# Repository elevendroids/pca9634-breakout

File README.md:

# PCA9634 Breakout Board

Small board for the 8 channel I2C-bus PWM LED driver from NXP - PCA9634 [Datasheet](https://www.nxp.com/docs/en/data-sheet/PCA9634.pdf)

Designed in KiCad 5.1.6

Schematic: [PDF](docs/pca9634-breakout.pdf)

License: [CC BY-SA 4.0](https://creativecommons.org/licenses/by-sa/4.0/)

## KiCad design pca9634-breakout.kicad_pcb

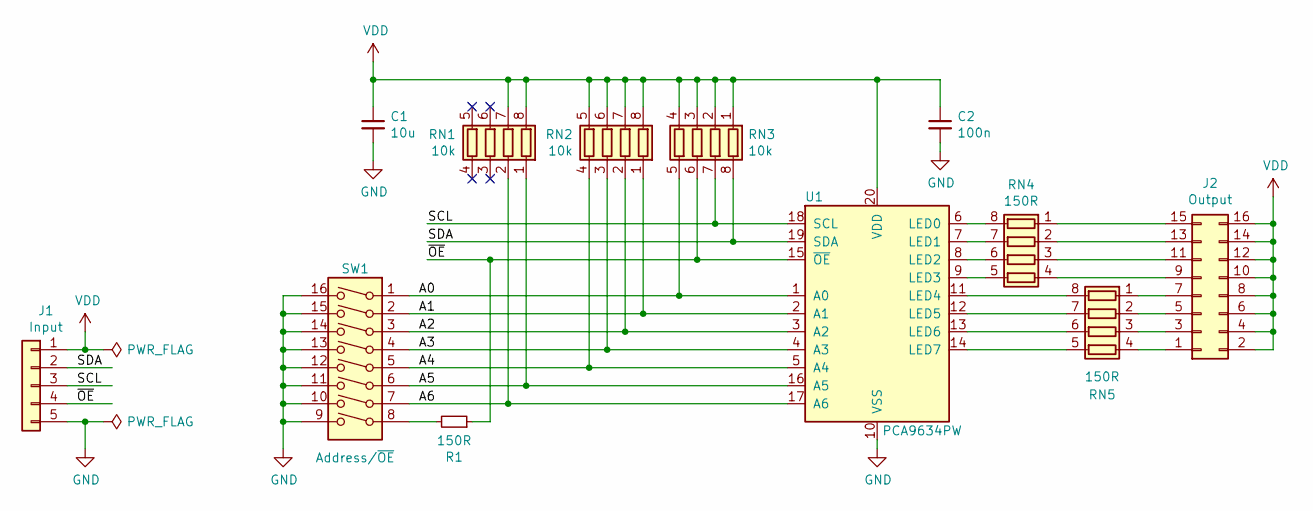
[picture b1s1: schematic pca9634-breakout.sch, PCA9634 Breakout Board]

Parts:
C1: 10u; C_0805_2012Metric
C2: 100n; C_0603_1608Metric
J1: Input; PinHeader_1x05_P2.54mm_Vertical
J2: Output; PinHeader_2x08_P2.54mm_Vertical
R1: 150R; R_0603_1608Metric
RN1, RN2, RN3: 10k; R_Array_Convex_4x0603
RN4, RN5: 150R; R_Array_Convex_4x0603
SW1: Address/~OE; SW_DIP_SPSTx08_Slide_6.7x21.88mm_W6.73mm_P2.54mm_LowProfile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
U1: PCA9634PW; TSSOP-20_4.4x6.5mm_P0.65mm

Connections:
/A0: RN3.5 (R4.2), SW1.1, U1.1 (A0)
/A1: RN2.1 (R1.1), SW1.2, U1.2 (A1)
/A2: RN2.2 (R2.1), SW1.3, U1.3 (A2)
/A3: RN2.3 (R3.1), SW1.4, U1.4 (A3)
/A4: RN2.4 (R4.1), SW1.5, U1.5 (A4)
/A5: RN1.1 (R1.1), SW1.6, U1.16 (A5)
/A6: RN1.2 (R2.1), SW1.7, U1.17 (A6)
/SCL: J1.3, RN3.7 (R2.2), U1.18 (SCL)
/SDA: J1.2, RN3.8 (R1.2), U1.19 (SDA)
/~OE: J1.4, R1.1, RN3.6 (R3.2), U1.15 (~OE)
GND: C1.2, C2.2, J1.5, SW1.9, SW1.10, SW1.11, SW1.12, SW1.13, SW1.14, SW1.15, SW1.16, U1.10 (VSS)
unnamed: J2.1, RN5.4 (R4.1)
unnamed: J2.3, RN5.3 (R3.1)
unnamed: J2.5, RN5.2 (R2.1)
unnamed: J2.7, RN5.1 (R1.1)
unnamed: J2.9, RN4.4 (R4.1)
unnamed: J2.11, RN4.3 (R3.1)
unnamed: J2.13, RN4.2 (R2.1)
unnamed: J2.15, RN4.1 (R1.1)
unnamed: R1.2, SW1.8
unnamed: RN4.5 (R4.2), U1.9 (LED3)
unnamed: RN4.6 (R3.2), U1.8 (LED2)
unnamed: RN4.7 (R2.2), U1.7 (LED1)
unnamed: RN4.8 (R1.2), U1.6 (LED0)
unnamed: RN5.5 (R4.2), U1.14 (LED7)
unnamed: RN5.6 (R3.2), U1.13 (LED6)
unnamed: RN5.7 (R2.2), U1.12 (LED5)
unnamed: RN5.8 (R1.2), U1.11 (LED4)
VDD: C1.1, C2.1, J1.1, J2.2, J2.4, J2.6, J2.8, J2.10, J2.12, J2.14, J2.16, RN1.7 (R2.2), RN1.8 (R1.2), RN2.5 (R4.2), RN2.6 (R3.2), RN2.7 (R2.2), RN2.8 (R1.2), RN3.1 (R1.1), RN3.2 (R2.1), RN3.3 (R3.1), RN3.4 (R4.1), U1.20 (VDD)

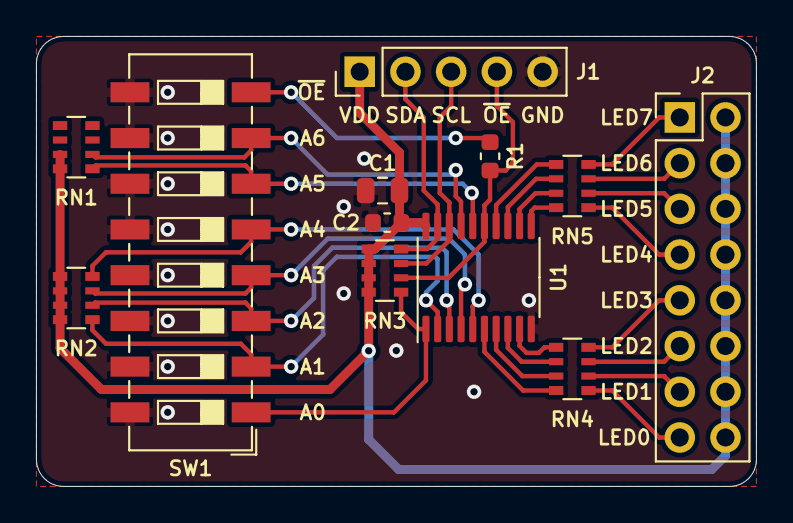
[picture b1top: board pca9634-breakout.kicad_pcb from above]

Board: 2 copper layers, 40.0 x 25.0 mm, 12 parts (0 on the bottom side), 29 nets.

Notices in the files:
pca9634-breakout.kicad_pcb:
© 2020 Michal Potrzebicz
License: CC BY-SA 4.0
